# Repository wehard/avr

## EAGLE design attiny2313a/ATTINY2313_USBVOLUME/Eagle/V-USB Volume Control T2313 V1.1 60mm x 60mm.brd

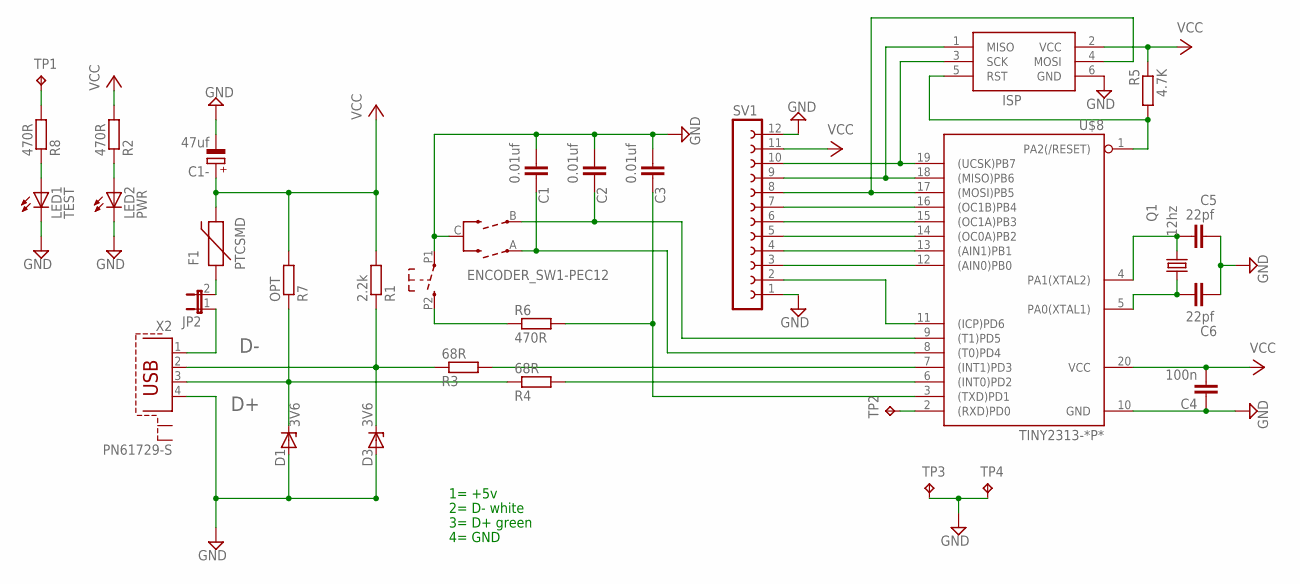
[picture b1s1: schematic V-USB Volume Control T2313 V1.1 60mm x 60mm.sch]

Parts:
C1, C2, C3: 0.01uf; C5B2.5
C1-: 47uf; E2,5-6
C4: 100n; C5B2.5
C5, C6: 22pf; C2.5-2
D1, D3: 3V6; DO34Z7
F1: PTCSMD; PTC-1206
ISP: AVRISP-6; AVRISP
JP2: JP1E; JP1
LED1: TEST; LED3MM
LED2: PWR; LED3MM
Q1: 12hz; HC49/S
R1: 2.2k; 0207/10
R2, R6: 470R; 0204/7
R3, R4: 68R; 0207/10
R5: 4.7K; 0204/7
R7: OPT; 0207/10
R8: 470R; 0207/10
SV1: FE12-1; FE12
SW3: ENCODER_SW1-PEC12; PEC12_INCREMENTAL_ENCODER
TP1, TP2: TPPAD1-13; P1-13
TP3, TP4: TPPAD1-20Y; P1-20Y
U$8: TINY2313-*P*; DIL20
X2: PN61729-S

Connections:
D+: D1.C, R4.1, R7.1, X2.3
D-: D3.C, R1.1, R3.1, X2.2
ENC-A-P3: C1.2, SW3.A, U$8.8 ((T0)PD4)
ENC-B-P2: C2.2, SW3.B, U$8.9 ((T1)PD5)
GND: C1.1, C1-.-, C2.1, C3.1, C4.1, C5.2, C6.2, D1.A, D3.A, ISP.6 (GND), LED1.K (C), LED2.K (C), SV1.1, SV1.12, SW3.C, SW3.P1 (1), TP3.TP, TP4.TP, U$8.10 (GND), X2.4
MUTE: C3.2, R6.2, U$8.3 ((TXD)PD1)
unnamed: ISP.4 (MOSI), SV1.8, U$8.17 ((MOSI)PB5)
unnamed: LED2.A, R2.1
unnamed: SV1.3, U$8.12 ((AIN0)PB0)
unnamed: SV1.4, U$8.13 ((AIN1)PB1)
unnamed: ISP.3 (SCK), SV1.10, U$8.19 ((UCSK)PB7)
unnamed: SV1.5, U$8.14 ((OC0A)PB2)
unnamed: C6.1, Q1.1, U$8.5 (PA0(XTAL1))
unnamed: SV1.6, U$8.15 ((OC1A)PB3)
unnamed: SV1.7, U$8.16 ((OC1B)PB4)
unnamed: R6.1, SW3.P2 (2)
unnamed: JP2.1, X2.1
unnamed: C5.1, Q1.2, U$8.4 (PA1(XTAL2))
unnamed: ISP.5 (RST), R5.2, U$8.1 (PA2(/RESET))
unnamed: R4.2, U$8.6 ((INT0)PD2)
unnamed: ISP.1 (MISO), SV1.9, U$8.18 ((MISO)PB6)
unnamed: SV1.2, U$8.11 ((ICP)PD6)
unnamed: R3.2, U$8.7 ((INT1)PD3)
unnamed: TP2.TP, U$8.2 ((RXD)PD0)
unnamed: F1.1, JP2.2
unnamed: LED1.A, R8.1
unnamed: R8.2, TP1.TP
VCC: C1-.+, C4.2, F1.2, ISP.2 (VCC), R1.2, R2.2, R5.1, R7.2, SV1.11, U$8.20 (VCC)

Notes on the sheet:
2= D- white
3= D+ green
4= GND
1= +5v

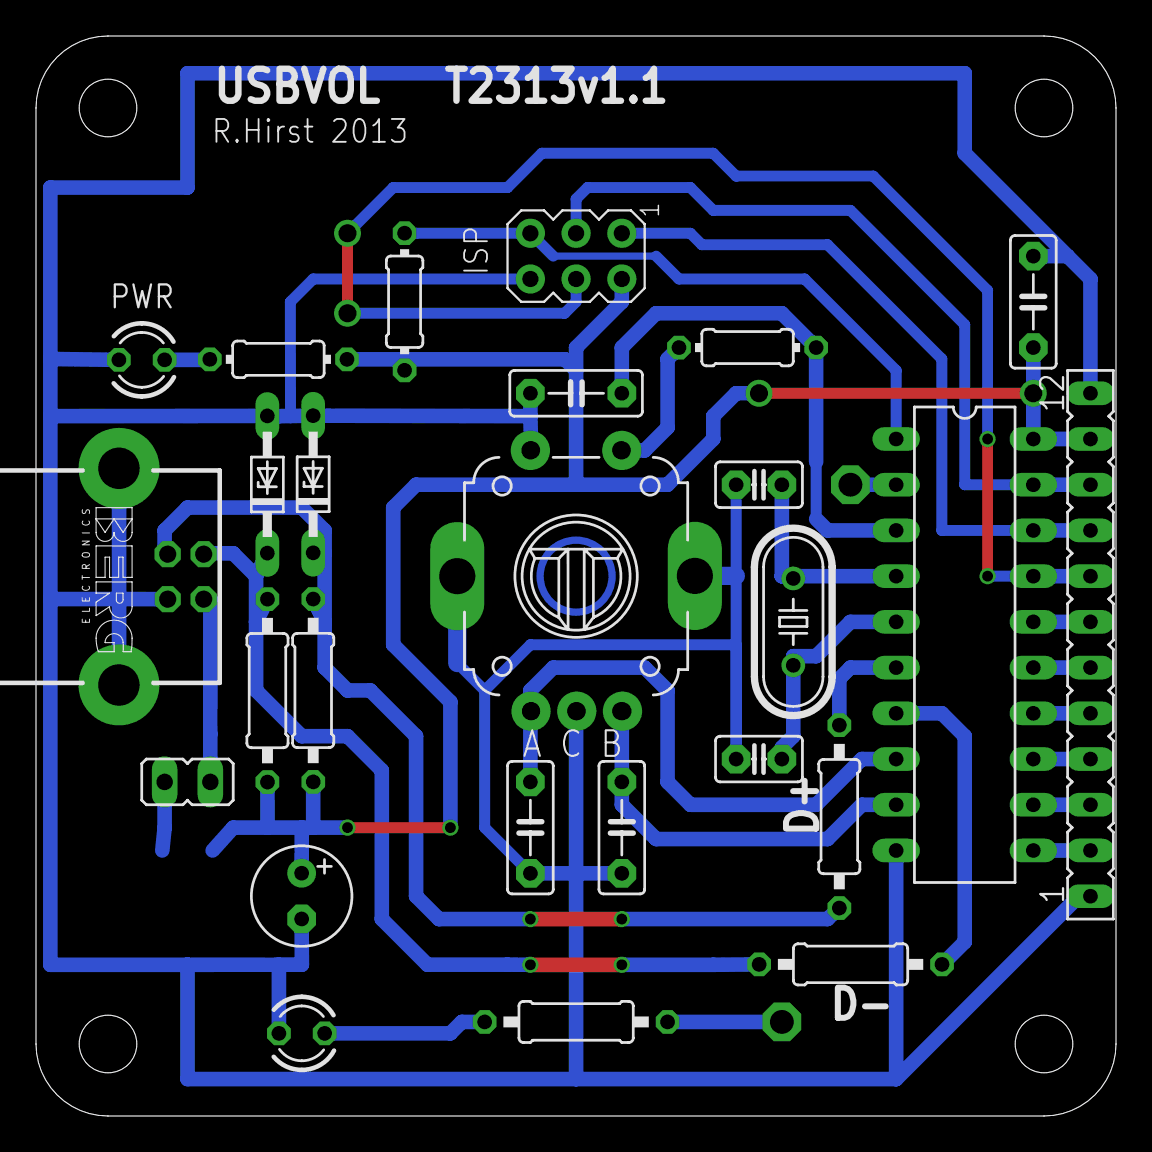
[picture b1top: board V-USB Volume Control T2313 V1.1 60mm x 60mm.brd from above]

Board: 2 copper layers, 60.0 x 60.0 mm, 32 parts (1 on the bottom side), 28 nets.

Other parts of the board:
U$2: DP6060_V1

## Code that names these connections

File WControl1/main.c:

/* Name: main.c
 * Project: HID-Test
 * Author: Christian Starkjohann
 * Creation Date: 2006-02-02
 * Tabsize: 4
 * Copyright: (c) 2006 by OBJECTIVE DEVELOPMENT Software GmbH
 * License: GNU GPL v2 (see License.txt) or proprietary (CommercialLicense.txt)
 * This Revision: $Id$
 */

#include <avr/io.h>
#include <avr/interrupt.h>
#include <avr/pgmspace.h>
#include <avr/wdt.h>

#include "usbdrv.h"
#include "oddebug.h"

/* ----------------------- hardware I/O abstraction ------------------------ */

/* pin assignments:
PB0	Key 1 A
PB1	Key 2 B
PB2	Key 3 C
PB3	Key 4 D
PB4	Key 5 E
PB5 	Key 6 F

PB6	Key 7 G
PB7	Key 8 H

PD1	debug tx
PD2	USB+ (int0)
PD3	USB-
PD4	Key 14
PD5	Key 15
PD6	Key 16
PD7	Key 17
*/

static void hardwareInit(void)
{
uchar	i, j;

    PORTB = 	0xff;   /* activate all pull-ups */
    DDRB = 	0b00000000;       /* all pins input */
    PORTD =	0b11110010;   /* 1111 0010 bin: activate pull-ups except on USB lines */
    DDRD =	0b00001111;    /* 0000 1101 bin: all pins input except USB (-> USB reset) */
	j = 0;
	while(--j){     /* USB Reset by device only required on Watchdog Reset */
		i = 0;
		while(--i); /* delay >10ms for USB reset */
	}
    DDRD = 0x02;    /* 0000 0010 bin: remove USB reset condition */
    /* configure timer 0 for a rate of 12M/(1024 * 256) = 45.78 Hz (~22ms) */
    TCCR0A = 5;      /* timer 0 prescaler: 1024 */
}

/* ------------------------------------------------------------------------- */

#define NUM_KEYS    8

/* The following function returns an index for the first key pressed. It
 * returns 0 if no key is pressed.
 */
static uchar    keyPressed(void)
{
uchar   i, mask, x;

    x = PINB;
    mask = 1;
    for(i=0;i<8;i++){
        if((x & mask) == 0)
            return i + 1;
        mask <<= 1;
    }
/*
    x = PIND;
    mask = 1 << 3;
    for(i=0;i<5;i++){
        if((x & mask) == 0)
            return i + 13;
        mask <<= 1;
    }
*/
    return 0;
}

/* ------------------------------------------------------------------------- */
/* ----------------------------- USB interface ----------------------------- */
/* ------------------------------------------------------------------------- */

static uchar    reportBuffer[2];    /* buffer for HID reports */
static uchar    idleRate;           /* in 4 ms units */

const PROGMEM char usbHidReportDescriptor[35] = {   /* USB report descriptor */
    0x05, 0x01,                    // USAGE_PAGE (Generic Desktop)
    0x09, 0x06,                    // USAGE (Keyboard)
    0xa1, 0x01,                    // COLLECTION (Application)
    0x05, 0x07,                    //   USAGE_PAGE (Keyboard)
    0x19, 0xe0,                    //   USAGE_MINIMUM (Keyboard LeftControl)
    0x29, 0xe7,                    //   USAGE_MAXIMUM (Keyboard Right GUI)
    0x15, 0x00,                    //   LOGICAL_MINIMUM (0)
    0x25, 0x01,                    //   LOGICAL_MAXIMUM (1)
    0x75, 0x01,                    //   REPORT_SIZE (1)
    0x95, 0x08,                    //   REPORT_COUNT (8)
    0x81, 0x02,                    //   INPUT (Data,Var,Abs)
    0x95, 0x01,                    //   REPORT_COUNT (1)
    0x75, 0x08,                    //   REPORT_SIZE (8)
    0x25, 0x65,                    //   LOGICAL_MAXIMUM (101)
    0x19, 0x00,                    //   USAGE_MINIMUM (Reserved (no event indicated))
    0x29, 0x65,                    //   USAGE_MAXIMUM (Keyboard Application)
    0x81, 0x00,                    //   INPUT (Data,Ary,Abs)
    0xc0                           // END_COLLECTION
};
/* We use a simplifed keyboard report descriptor which does not support the
 * boot protocol. We don't allow setting status LEDs and we only allow one
 * simultaneous key press (except modifiers). We can therefore use short
 * 2 byte input reports.
 * The report descriptor has been created with usb.org's "HID Descriptor Tool"
 * which can be downloaded from http://www.usb.org/developers/hidpage/.
 * Redundant entries (such as LOGICAL_MINIMUM and USAGE_PAGE) have been omitted
 * for the second INPUT item.
 */

/* Keyboard usage values, see usb.org's HID-usage-tables document, chapter
 * 10 Keyboard/Keypad Page for more codes.
 */
#define MOD_CONTROL_LEFT    (1<<0)
#define MOD_SHIFT_LEFT      (1<<1)
#define MOD_ALT_LEFT        (1<<2)
#define MOD_GUI_LEFT        (1<<3)
#define MOD_CONTROL_RIGHT   (1<<4)
#define MOD_SHIFT_RIGHT     (1<<5)
#define MOD_ALT_RIGHT       (1<<6)
#define MOD_GUI_RIGHT       (1<<7)

#define KEY_A       4
#define KEY_B       5
#define KEY_C       6
#define KEY_D       7
#define KEY_E       8
#define KEY_F       9
#define KEY_G       10
#define KEY_H       11
#define KEY_I       12
#define KEY_J       13
#define KEY_K       14
#define KEY_L       15
#define KEY_M       16
#define KEY_N       17
#define KEY_O       18
#define KEY_P       19
#define KEY_Q       20
#define KEY_R       21
#define KEY_S       22
#define KEY_T       23
#define KEY_U       24
#define KEY_V       25
#define KEY_W       26
#define KEY_X       27
#define KEY_Y       28
#define KEY_Z       29
#define KEY_1       30
#define KEY_2       31
#define KEY_3       32
#define KEY_4       33
#define KEY_5       34
#define KEY_6       35
#define KEY_7       36
#define KEY_8       37
#define KEY_9       38
#define KEY_0       39

#define KEY_F1      58
#define KEY_F2      59
#define KEY_F3      60
#define KEY_F4      61
#define KEY_F5      62
#define KEY_F6      63
#define KEY_F7      64
#define KEY_F8      65
#define KEY_F9      66
#define KEY_F10     67
#define KEY_F11     68
#define KEY_F12     69

static const uchar  keyReport[NUM_KEYS + 1][2] PROGMEM = {
/* none */  {0, 0},                     /* no key pressed */
/*  1 */    {MOD_SHIFT_LEFT, KEY_A},
/*  2 */    {MOD_SHIFT_LEFT, KEY_B},
/*  3 */    {MOD_SHIFT_LEFT, KEY_C},
/*  4 */    {MOD_SHIFT_LEFT, KEY_D},
/*  5 */    {MOD_SHIFT_LEFT, KEY_E},
/*  6 */    {MOD_SHIFT_LEFT, KEY_F},
/*  7 */    {MOD_SHIFT_LEFT, KEY_G},
/*  8 */    {MOD_SHIFT_LEFT, KEY_H},
};

static void buildReport(uchar key)
{
/* This (not so elegant) cast saves us 10 bytes of program memory */
    *(int *)reportBuffer = pgm_read_word(keyReport[key]);
}

uchar	usbFunctionSetup(uchar data[8])
{
usbRequest_t    *rq = (void *)data;

    usbMsgPtr = reportBuffer;
    if((rq->bmRequestType & USBRQ_TYPE_MASK) == USBRQ_TYPE_CLASS){    /* class request type */
        if(rq->bRequest == USBRQ_HID_GET_REPORT){  /* wValue: ReportType (highbyte), ReportID (lowbyte) */
            /* we only have one report type, so don't look at wValue */
            buildReport(keyPressed());
            return sizeof(reportBuffer);
        }else if(rq->bRequest == USBRQ_HID_GET_IDLE){
            usbMsgPtr = &idleRate;
            return 1;
        }else if(rq->bRequest == USBRQ_HID_SET_IDLE){
            idleRate = rq->wValue.bytes[1];
        }
    }else{
        /* no vendor specific requests implemented */
    }
	return 0;
}

/* ------------------------------------------------------------------------- */

int	main(void)
{
uchar   key, lastKey = 0, keyDidChange = 0;
uchar   idleCounter = 0;

	wdt_enable(WDTO_2S);
    hardwareInit();
	odDebugInit();
	usbInit();
	sei();
    DBG1(0x00, 0, 0);
	for(;;){	/* main event loop */
		wdt_reset();
		usbPoll();
        key = keyPressed();
        if(lastKey != key){
            lastKey = key;
            keyDidChange = 1;
        }
        if(TIFR & (1<<TOV0)){   /* 22 ms timer */
            TIFR = 1<<TOV0;
            if(idleRate != 0){
                if(idleCounter > 4){
                    idleCounter -= 5;   /* 22 ms in units of 4 ms */
                }else{
                    idleCounter = idleRate;
                    keyDidChange = 1;
                }
            }
        }
        if(keyDidChange && usbInterruptIsReady()){
            keyDidChange = 0;
            /* use last key and not current key status in order to avoid lost
               changes in key status. */
            buildReport(lastKey);
            usbSetInterrupt(reportBuffer, sizeof(reportBuffer));
        }
	}
	return 0;
}

/* ------------------------------------------------------------------------- */

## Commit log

2015-09-21 Started working on getting value from rotary encoder
2015-09-21 ATMega32 is running at 1Mhz. This is the default for this MCU. AVRGCC was compiling for 8Mhz. Delays were funny. Seems to be working now. 1Mhz should be enough for this application. Always check Make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
2015-09-22 Trying to get rotary encoder to work...
2015-09-22 Encoder is working! Only it steps in two increments...
2015-09-22 Encoder is working! Now for the menu selection stuff!
2015-09-23 Added saving values to EEPROM
2015-09-23 Added more values to play with. Also LCD functions Send_A_String_XY and Send_An_Integer_XY
2015-09-23 Added source code from DevPi to repository. Never mind the mess.
2019-05-15 Merged other newer? project
2019-09-09 Renamed folders.
